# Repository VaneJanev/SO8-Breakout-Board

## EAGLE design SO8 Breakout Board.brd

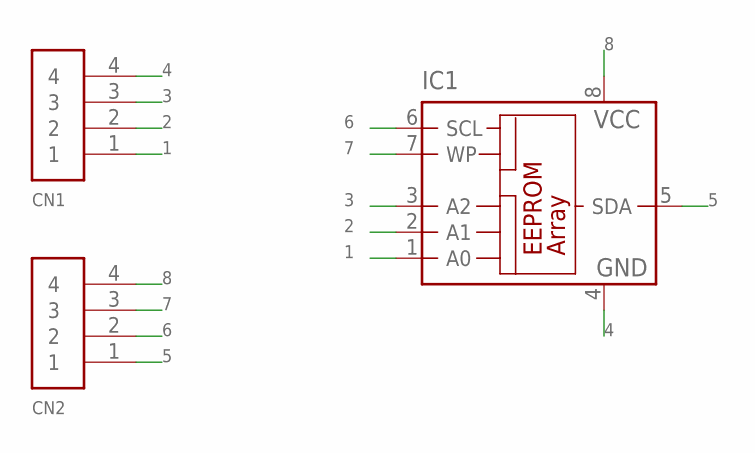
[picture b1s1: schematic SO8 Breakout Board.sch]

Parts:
CN1, CN2: 1X4-BIG; 1X04-BIG
IC1: 24AA01SN; SO-08

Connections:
1: CN1.1, IC1.1 (A0)
2: CN1.2, IC1.2 (A1)
3: CN1.3, IC1.3 (A2)
4: CN1.4, IC1.4 (GND)
5: CN2.1, IC1.5 (SDA)
6: CN2.2, IC1.6 (SCL)
7: CN2.3, IC1.7 (WP)
8: CN2.4, IC1.8 (VCC)

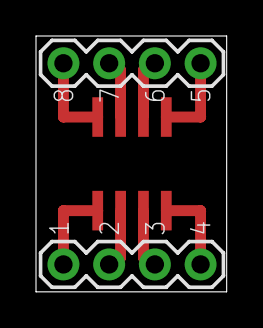
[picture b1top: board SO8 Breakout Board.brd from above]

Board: 2 copper layers, 10.6 x 14.2 mm, 3 parts (0 on the bottom side), 8 nets.

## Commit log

2015-06-03 :confetti_ball: Added .gitattributes
2015-06-03 SO8 Breakout Board
    Eagle Files
